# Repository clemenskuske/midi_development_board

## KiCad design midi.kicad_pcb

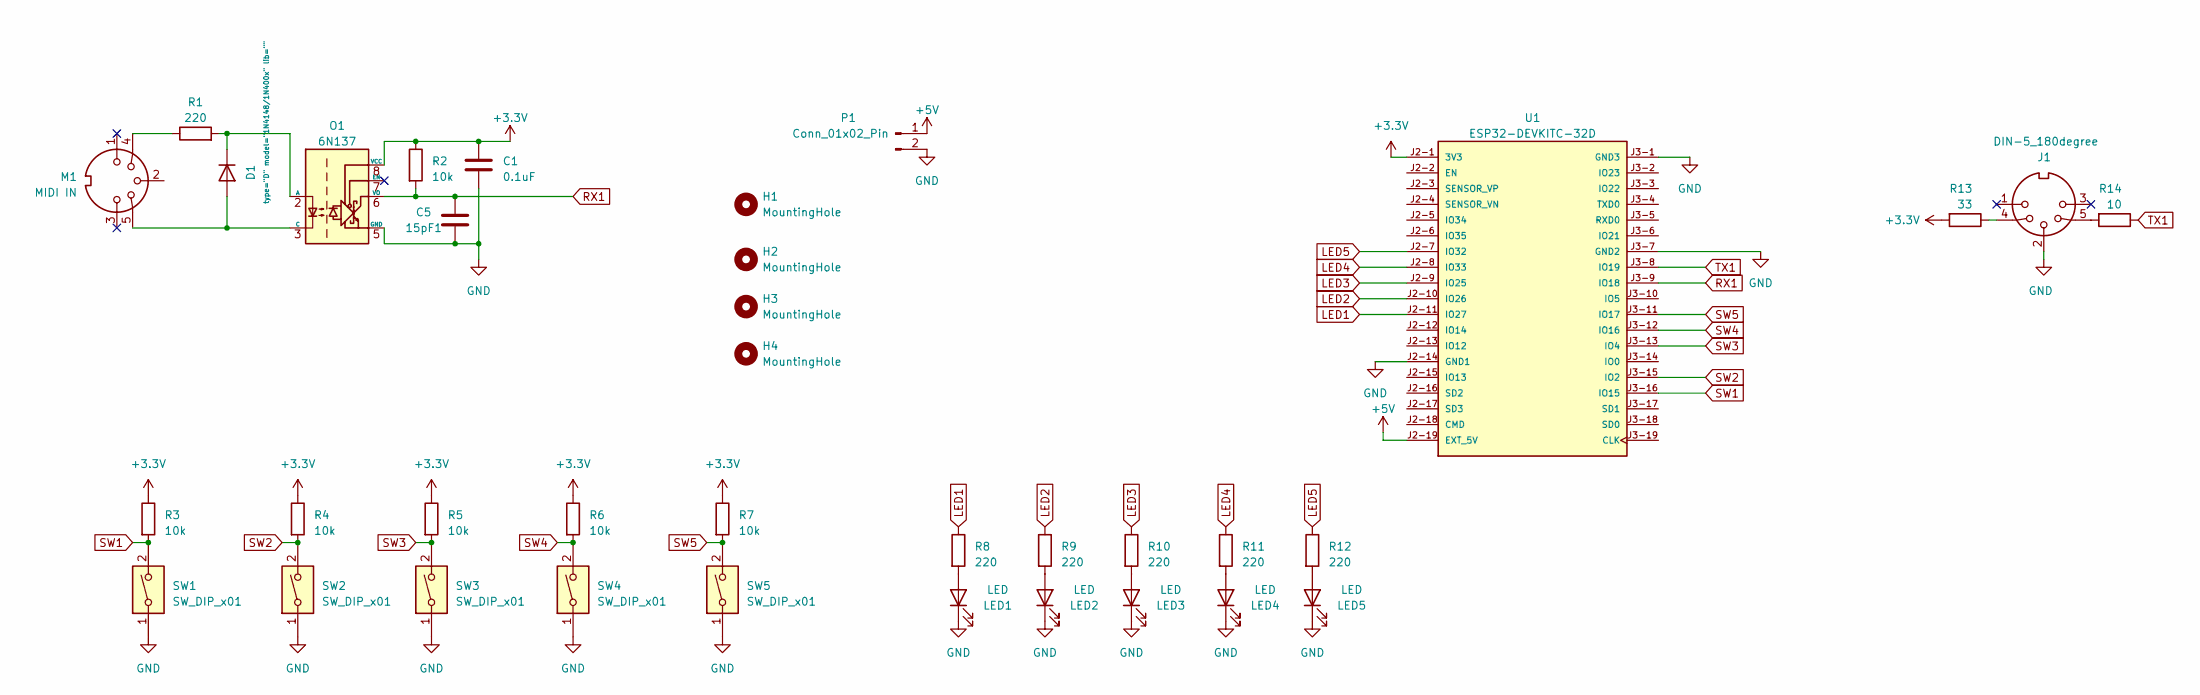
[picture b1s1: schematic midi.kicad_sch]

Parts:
15pF1: C5; C_0805_2012Metric
C1: 0.1uF; CP_EIA-3528-12_Kemet-T
D1: type="D" model="1N4148/1N400x" lib=""; SOD-80
H1, H2, H3, H4: MountingHole; MountingHole_3.2mm_M3
J1: DIN-5_180degree; midi
LED1, LED2, LED3, LED4, LED5: LED
M1: MIDI IN; midi
O1: 6N137; optocoppler
P1: Conn_01x02_Pin; chinch
R1, R8, R9, R10, R11, R12: 220; R_0603_1608Metric
R2, R3, R4, R5, R6, R7: 10k; R_0603_1608Metric
R13: 33; R_0402_1005Metric
R14: 10; R_0402_1005Metric
SW1, SW2, SW3, SW4, SW5: SW_DIP_x01; switch
U1: ESP32-DEVKITC-32D; MODULE_ESP32-DEVKITC-32D; PARTREV V4

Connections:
+3.3V: C1.1, O1.8 (VCC), R2.1, R3.1, R4.1, R5.1, R6.1, R7.1, R13.2, U1.J2-1 (3V3)
+5V: P1.1, U1.J2-19 (EXT_5V)
GND: 15pF1.2, C1.2, J1.2, LED1.1 (K), LED2.1 (K), LED3.1 (K), LED4.1 (K), LED5.1 (K), O1.5 (GND), P1.2, SW1.1, SW2.1, SW3.1, SW4.1, SW5.1, U1.J2-14 (GND1), U1.J3-1 (GND3), U1.J3-7 (GND2)
LED1: R8.1, U1.J2-11 (IO27)
LED2: R9.1, U1.J2-10 (IO26)
LED3: R10.1, U1.J2-9 (IO25)
LED4: R11.1, U1.J2-8 (IO33)
LED5: R12.1, U1.J2-7 (IO32)
unnamed: D1.1 (A), M1.5, O1.3 (C)
unnamed: D1.2 (K), O1.2 (A), R1.2
unnamed: J1.4, R13.1
unnamed: J1.5, R14.2
unnamed: LED1.2 (A), R8.2
unnamed: LED2.2 (A), R9.2
unnamed: LED3.2 (A), R10.2
unnamed: LED4.2 (A), R11.2
unnamed: LED5.2 (A), R12.2
unnamed: M1.4, R1.1
RX1: 15pF1.1, O1.6 (VO), R2.2, U1.J3-9 (IO18)
SW1: R3.2, SW1.2, U1.J3-16 (IO15)
SW2: R4.2, SW2.2, U1.J3-15 (IO2)
SW3: R5.2, SW3.2, U1.J3-13 (IO4)
SW4: R6.2, SW4.2, U1.J3-12 (IO16)
SW5: R7.2, SW5.2, U1.J3-11 (IO17)
TX1: R14.1, U1.J3-8 (IO19)

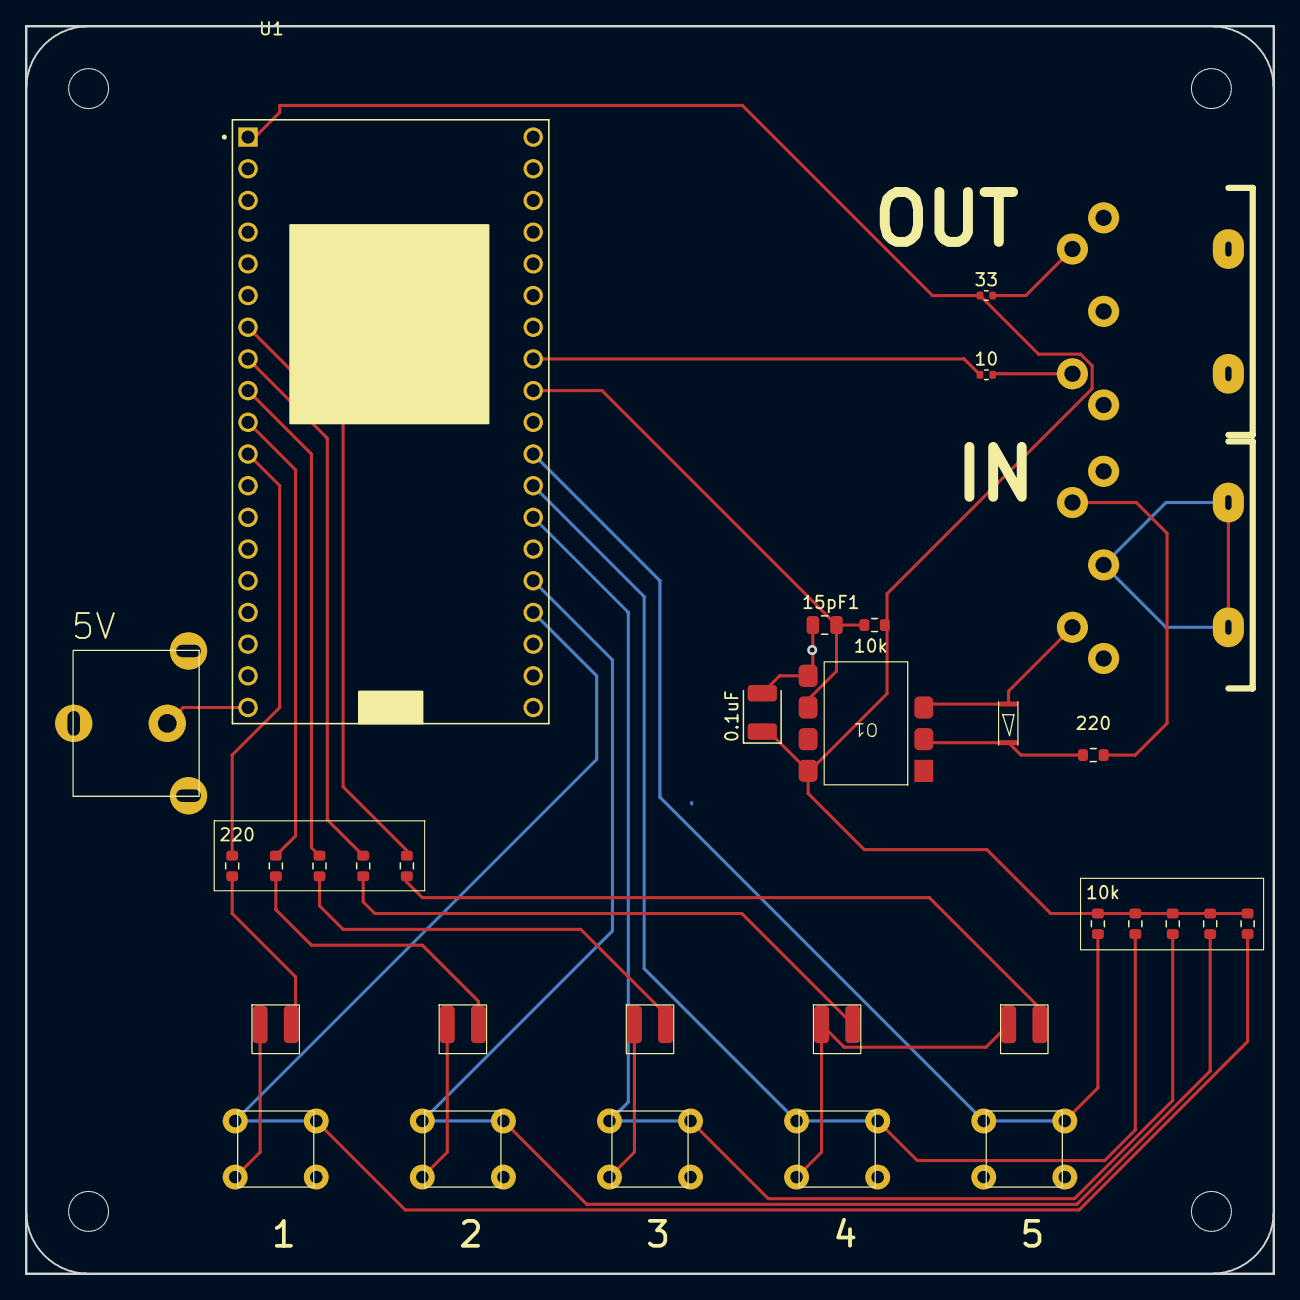
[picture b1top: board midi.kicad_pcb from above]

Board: 2 copper layers, 100.0 x 100.0 mm, 36 parts (0 on the bottom side), 25 nets.

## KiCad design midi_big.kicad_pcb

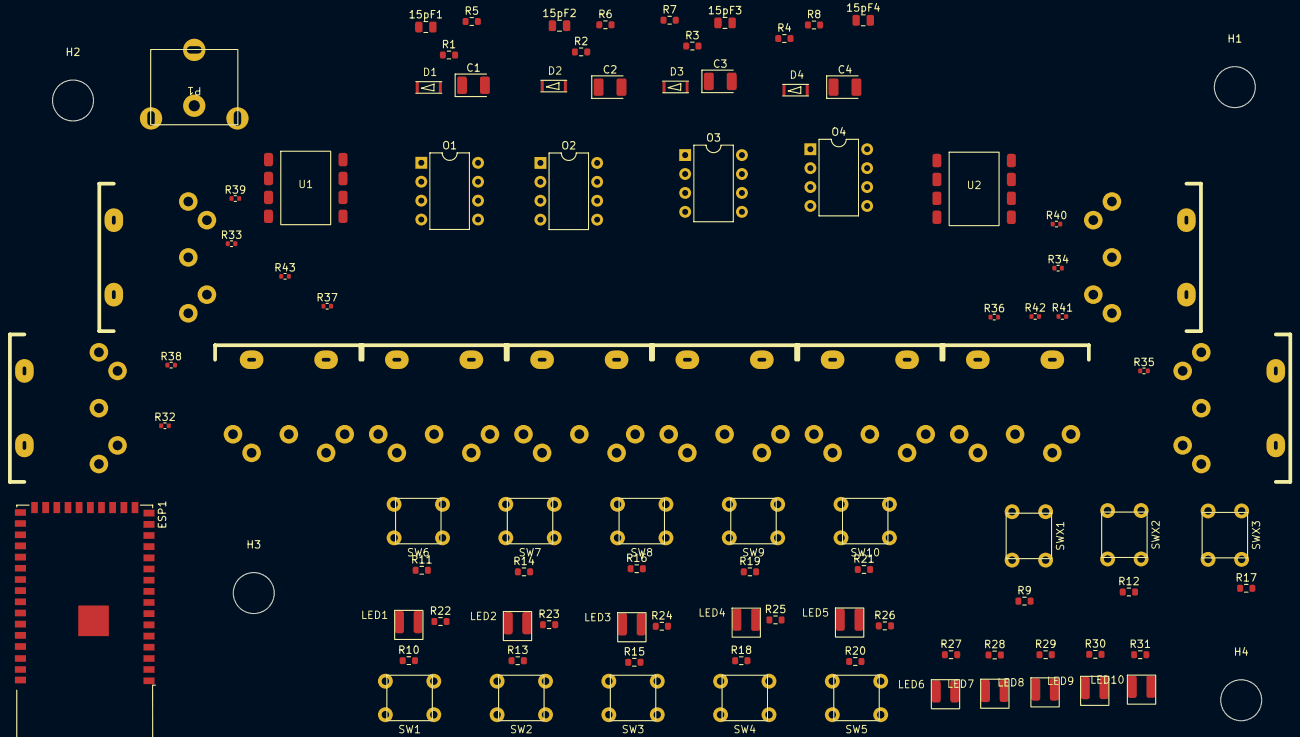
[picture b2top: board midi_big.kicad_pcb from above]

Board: 2 copper layers, 100 parts (0 on the bottom side), 73 nets, no tracks yet.

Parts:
15pF1: C5; C_0805_2012Metric
15pF2: C6; C_0805_2012Metric
15pF3: C7; C_0805_2012Metric
15pF4: C; C_0805_2012Metric
C1, C2, C3, C4: 0.1uF; CP_EIA-3528-12_Kemet-T
D1, D2, D3, D4: type="D" model="1N4148/1N400x" lib=""; SOD-80
ESP1: ESP32-S2-WROVER-I; ESP32-S2-WROVER
H1, H2, H3, H4: MountingHole; MountingHole_5.5mm
J1, J2, J3, J4, J5, J6: DIN-5_180degree; midi
LED1, LED2, LED3, LED4, LED5, LED6, LED7, LED8, LED9, LED10: LED
M1, M2, M3: MIDI IN; midi
M4: locked; midi
O1, O2, O3, O4: 6N137; DIP-8_W7.62mm
P1: Conn_01x02_Pin; chinch
R1, R2, R3, R4, R22, R23, R24, R25, R26, R27, R28, R29, R30, R31: 220; R_0603_1608Metric
R5, R6, R7, R8, R9, R10, R11, R12, R13, R14, R15, R16, R17, R18, R19, R20, R21: 10k; R_0603_1608Metric
R32, R33, R34, R35, R36, R37: 33; R_0402_1005Metric
R38, R39, R40, R41, R42, R43: 10; R_0402_1005Metric
SW1, SW2, SW3, SW4, SW5, SW6, SW7, SW8, SW9, SW10: SW_DIP_x01; switch
SWX1, SWX2, SWX3: SW_DIP_x01; switch
U1, U2: 74LCX07; optocoppler

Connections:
+3.3V: ESP1.2 (3V3), P1.1, R9.1, R10.1, R11.1, R12.1, R13.1, R14.1, R15.1, R16.1, R17.1, R18.1, R19.1, R20.1, R21.1, R32.2, R33.2, R34.2, R35.2, R36.2, R37.2
GND: 15pF1.2, 15pF2.2, 15pF3.2, 15pF4.2, C1.2, C2.2, C3.2, C4.2, ESP1.1 (GND), ESP1.26 (GND), ESP1.42 (GND), ESP1.43 (GND), J1.2, J2.2, J3.2, J4.2, J5.2, J6.2, LED1.1 (K), LED2.1 (K), LED3.1 (K), LED4.1 (K), LED5.1 (K), LED6.1 (K), LED7.1 (K), LED8.1 (K), LED9.1 (K), LED10.1 (K), O1.5 (GND), O2.5 (GND), O3.5 (GND), O4.5 (GND), P1.2, SW1.1, SW2.1, SW3.1, SW4.1, SW5.1, SW6.1, SW7.1, SW8.1, SW9.1, SW10.1, SWX1.1, SWX2.1, SWX3.1, U1.7 (GND), U2.7 (GND)
LED1: ESP1.13 (IO10), R22.1
LED2: ESP1.14 (IO11), R24.1
LED3: ESP1.15 (IO12), R26.1
LED4: ESP1.16 (IO13), R28.1
LED5: ESP1.17 (IO14), R30.1
LED6: ESP1.18 (IO15), R23.1
LED7: ESP1.19 (IO16), R25.1
LED8: ESP1.20 (IO17), R27.1
LED9: ESP1.21 (IO18), R29.1
LED10: ESP1.35 (IO41), R31.1
unnamed: D1.1 (A), M1.5, O1.3 (C)
unnamed: D1.2 (K), O1.2 (A), R1.2
unnamed: D2.1 (A), M2.5, O2.3 (C)
unnamed: D2.2 (K), O2.2 (A), R2.2
unnamed: D3.1 (A), M3.5, O3.3 (C)
unnamed: D3.2 (K), O3.2 (A), R3.2
unnamed: D4.1 (A), M4.5, O4.3 (C)
unnamed: D4.2 (K), O4.2 (A), R4.2
unnamed: J1.4, R32.1
unnamed: J1.5, R38.2
unnamed: J2.4, R33.1
unnamed: J2.5, R39.2
unnamed: J3.4, R34.1
unnamed: J3.5, R40.2
unnamed: J4.4, R35.1
unnamed: J4.5, R41.2
unnamed: J5.4, R36.1
unnamed: J5.5, R42.2
unnamed: J6.4, R37.1
unnamed: J6.5, R43.2
unnamed: LED1.2 (A), R22.2
unnamed: LED2.2 (A), R23.2
unnamed: LED3.2 (A), R24.2
unnamed: LED4.2 (A), R25.2
unnamed: LED5.2 (A), R26.2
unnamed: LED6.2 (A), R27.2
unnamed: LED7.2 (A), R28.2
unnamed: LED8.2 (A), R29.2
unnamed: LED9.2 (A), R30.2
unnamed: LED10.2 (A), R31.2
unnamed: M1.4, R1.1
unnamed: M2.4, R2.1
unnamed: M3.4, R3.1
unnamed: M4.4, R4.1
unnamed: R38.1, U1.2
unnamed: R39.1, U1.6
unnamed: R41.1, U2.2
unnamed: R42.1, U2.6
unnamed: U1.1, U1.4
unnamed: U1.5, U1.8
unnamed: U2.1, U2.4
unnamed: U2.5, U2.8
RX0: C1.1, O1.8 (VCC), R5.1
RX1: C2.1, ESP1.3 (IO00), O2.8 (VCC), R6.1
RX2: C3.1, ESP1.4 (IO01), O3.8 (VCC), R7.1
RX3: C4.1, ESP1.5 (IO02), O4.8 (VCC), R8.1
SW1: ESP1.34 (IO40), R10.2
SW2: ESP1.33 (IO39), R13.2
SW3: ESP1.32 (IO38), R15.2
SW4: ESP1.31 (IO37), R18.2
SW5: ESP1.30 (IO36), R20.2
SW6: ESP1.29 (IO35), R11.2
SW7: ESP1.28 (IO34), R14.2
SW8: ESP1.27 (IO33), R16.2
SW9: ESP1.25 (IO26), R19.2
SW10: ESP1.24 (IO21), R21.2
SWX1: ESP1.40 (IO46), R9.2
SWX2: ESP1.39 (IO45), R12.2
SWX3: ESP1.36 (IO42), R17.2
TX1: ESP1.7 (IO04), U1.3
VCC: 15pF1.1, 15pF2.1, 15pF3.1, 15pF4.1, O1.6 (VO), O2.6 (VO), O3.6 (VO), O4.6 (VO), R5.2, R6.2, R7.2, R8.2

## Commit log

2023-07-03 update used pins
